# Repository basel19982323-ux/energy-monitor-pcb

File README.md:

# ESP32-C3 Solar Energy Monitor (PCB)

A 2-layer, 60 × 38 mm board that measures the **voltage, current and power** of a 50 W / 12 V solar panel and reports them over **Wi-Fi**.

> **Status:** designed and checked in KiCad 10 (ERC 0 errors, DRC 0 errors, 0 unconnected). **Not yet fabricated or tested on hardware.** Firmware (C, ESP-IDF) is written and tested in simulation: see [Firmware](#firmware).

| Top | Bottom |
|---|---|
|  |  |

---

## What it does

The panel's current flows through the board, from **J2 (Solar IN)** to **J3 (Load OUT)**, through a small 20 mΩ shunt resistor. The board works in five steps:

1. **Feed:** 5 V comes in through USB-C (J1). R1/R2 (5.1 kΩ on CC1/CC2) tell the USB source that this is a 5 V sink.
2. **Clean:** an AP2112K-3.3 LDO regulator (U2) makes a steady 3.3 V supply.
3. **Measure:** an INA226 (U1) measures the panel voltage and the current through the 20 mΩ shunt (R3).
4. **Think:** an ESP32-C3-WROOM-02 module (U3) reads the INA226 over I²C (address 0x40) and calculates power.
5. **Send:** the ESP32-C3 sends the readings over Wi-Fi. USB data (D+/D−) goes to the ESP32-C3's native USB for programming.

## Key numbers

| Item | Value |
|---|---|
| Target panel | 50 W, 12 V (Imp 2.84 A, Isc 3.13 A, Voc 20.8 V) |
| Shunt | 20 mΩ, 2512, 1 %, 2 W, Kelvin-connected |
| Max measurable current | 81.92 mV ÷ 0.02 Ω ≈ **4.1 A** (INA226 full-scale shunt voltage) |
| Shunt power at 4.1 A | 4.1² × 0.02 ≈ 0.34 W (well below the 2 W rating) |
| Logic supply | 5 V USB-C → 3.3 V (AP2112K, 600 mA max) |
| Board | 2 layers, 1.6 mm, 60 × 38 mm |

## Design decisions

- **Trace widths by net class** (IPC-2221): signals 0.25 mm, power (VBUS, +3V3) 0.5 mm, high current (PV_IN, LOAD_OUT) 2.1 mm for ~4 A.
- **Kelvin sensing:** the INA226 sense traces leave from the inner edges of the shunt pads, so the high current does not flow through the measurement traces.
- **Ground:** ground pours on both layers, joined by stitching vias, so every return current has a short path home.
- **Decoupling:** 100 nF + 10 µF placed at the ESP32-C3 3V3 pin (smallest capacitor closest), 100 nF at the INA226, 1 µF at the LDO input and output.
- **Antenna:** the ESP32-C3 antenna overhangs the board edge with no copper underneath, following Espressif's layout guidelines.
- **Boot and reset:** RESET (EN) with an RC start-up delay (10 kΩ + 1 µF), a BOOT button on IO9, and pull-ups on the strapping pins IO2/IO8/IO9.
- **Manufacturing:** checked against JLCPCB's capabilities (0.2 mm clearance, 0.3 mm vias, 0.15 mm silkscreen line width).

## Firmware

C firmware for the ESP32-C3 (ESP-IDF + FreeRTOS), tested in the Wokwi simulator with a simulated INA226. Not yet run on the real board. Full details, code structure and test results: **[firmware/README.md](firmware/README.md)**.

- Reads voltage, current and power from the INA226 over I²C every second (CAL = 2048 → 125 µA per bit)
- Latched alarm on overcurrent (> 3.5 A), overvoltage (> 22 V) or a missing sensor; reset with the BOOT button
- Re-writes the INA226 calibration automatically after the sensor stops answering and comes back
- Publishes the readings as JSON over Wi-Fi + MQTT
- 9 simulation tests (normal, faults, latch, reset, sensor removed, Wi-Fi): all pass

## Repository contents

```
hardware/     KiCad 10 project (schematic, PCB, project file)
production/   JLCPCB-ready files: Gerbers + drill (zip), BOM, CPL (positions)
firmware/     ESP32-C3 firmware (ESP-IDF, C) + Wokwi simulation files
docs/         Schematic PDF, 3D renders, layout preview, firmware screenshot
```

- **Schematic (PDF):** [docs/energy-monitor.pdf](docs/energy-monitor.pdf)
- **Gerbers + drill:** [production/energy-monitor_v0.2.zip](production/energy-monitor_v0.2.zip)
- **BOM** (with LCSC part numbers): [production/energy-monitor_v0.2_bom.csv](production/energy-monitor_v0.2_bom.csv)
- **CPL / pick-and-place:** [production/energy-monitor_v0.2_positions.csv](production/energy-monitor_v0.2_positions.csv)

## Bill of materials (summary)

| Ref | Part | LCSC |
|---|---|---|
| U1 | TI INA226AIDGSR (current/power monitor) | C49851 |
| U2 | Diodes AP2112K-3.3TRG1 (3.3 V LDO) | C51118 |
| U3 | Espressif ESP32-C3-WROOM-02-N4 | C2934560 |
| J1 | HRO TYPE-C-31-M-12 (USB-C) | C165948 |
| J2, J3 | Phoenix MKDS 1,5/2-5,08 terminal block | C480516 |
| R3 | 20 mΩ 2512 2 W shunt | C5375423 |
| SW1, SW2 | Omron B3F-1020 tactile switch | C722171 |
| R, C | 0805 passives (see BOM) | — |

## Notes

- The 3D model of the USB-C connector is not included (it is not from the official KiCad library), so J1 appears without a body in the 3D viewer. The PCB and fabrication files are not affected.
- Next steps: order the boards, run the firmware on real hardware and compare the readings against a reference meter, and add a status LED (rev 0.3).

## Tools

KiCad 10 · JLCPCB design rules · Fabrication Toolkit plugin · ESP-IDF (C, FreeRTOS) · Wokwi simulator

## License

Hardware design licensed under the **CERN Open Hardware Licence v2 – Permissive** ([CERN-OHL-P-2.0](LICENSE)). Firmware licensed under **MIT** ([firmware/LICENSE](firmware/LICENSE)).

© 2026 Basel Haijar

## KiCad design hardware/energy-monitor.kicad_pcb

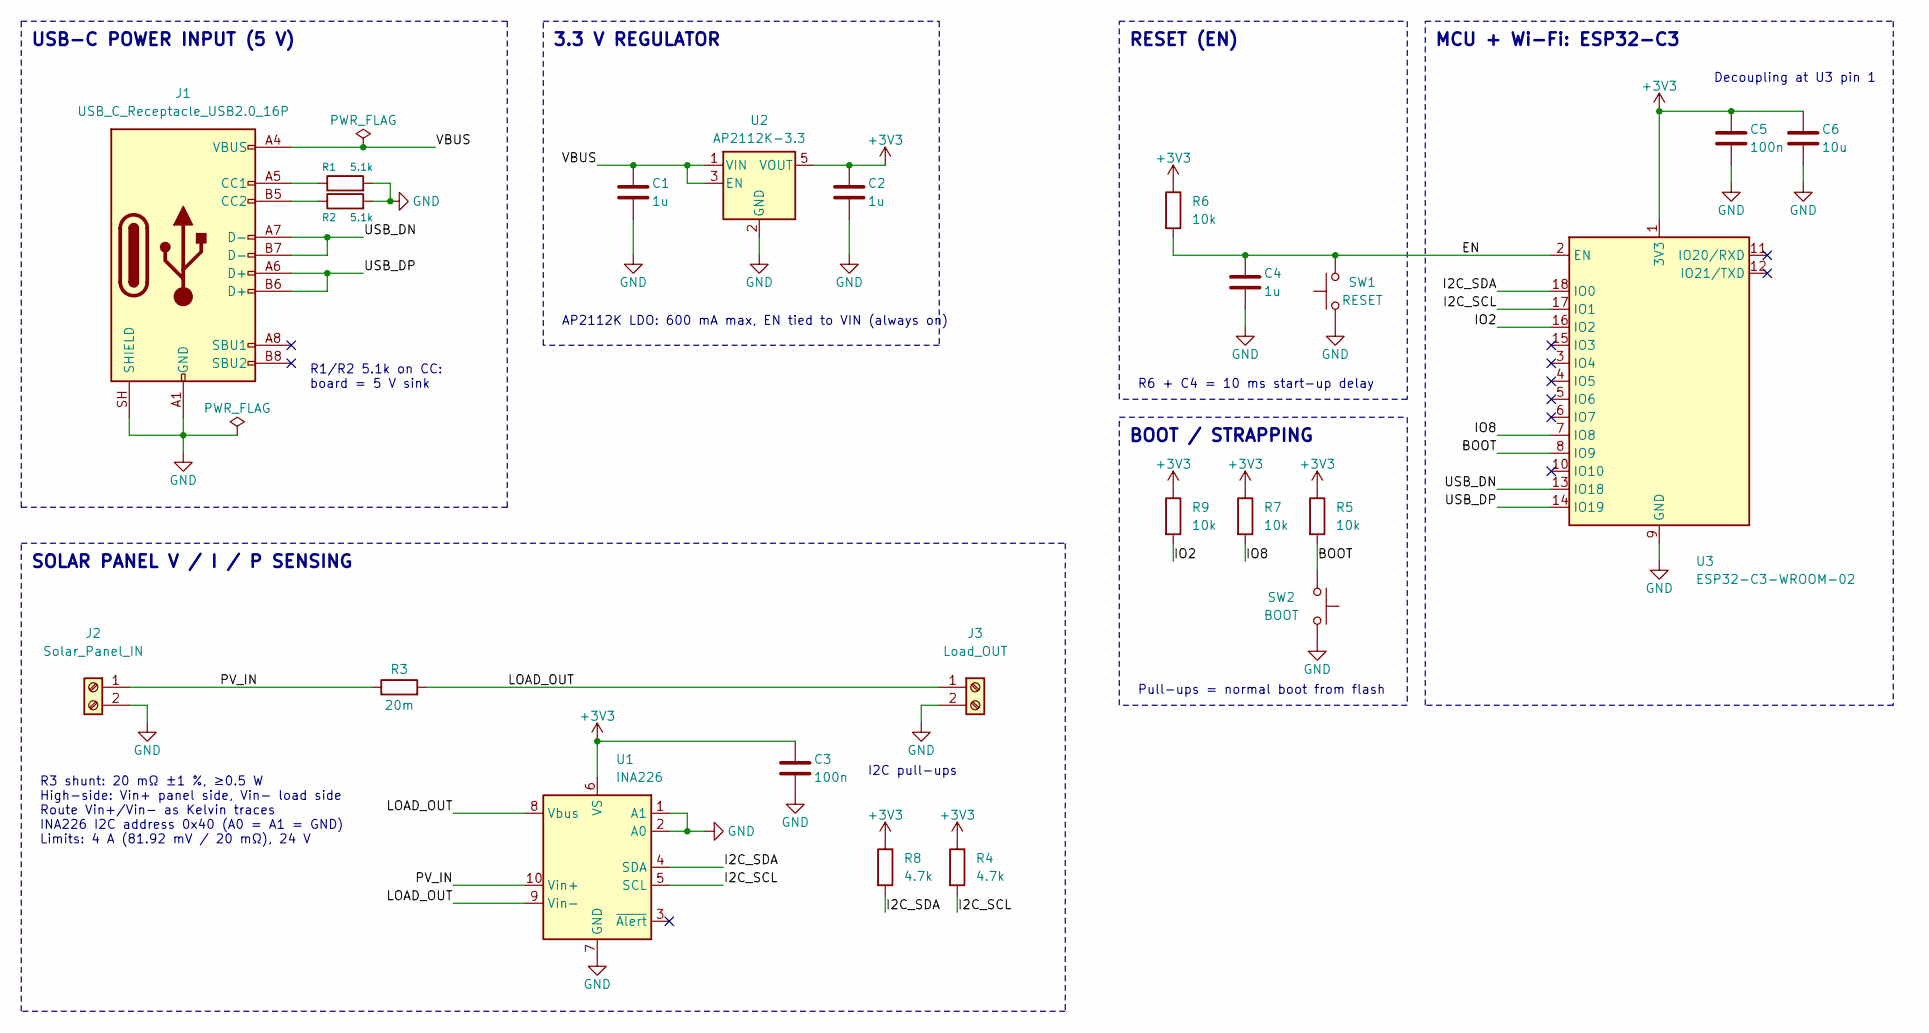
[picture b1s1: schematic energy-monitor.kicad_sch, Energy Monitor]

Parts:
C1, C2, C4: 1u; C_0805_2012Metric; LCSC C28323
C3, C5: 100n; C_0805_2012Metric; LCSC C49678
C6: 10u; C_0805_2012Metric; LCSC C15850
J1: USB_C_Receptacle_USB2.0_16P; USB_C_Receptacle_HRO_TYPE-C-31-M-12; LCSC C165948
J2: Solar_Panel_IN; TerminalBlock_Phoenix_MKDS-1,5-2-5.08_1x02_P5.08mm_Horizont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; LCSC C480516
J3: Load_OUT; TerminalBlock_Phoenix_MKDS-1,5-2-5.08_1x02_P5.08mm_Horizont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; LCSC C480516
R1, R2: 5.1k; R_0805_2012Metric; LCSC C27834
R3: 20m; R_2512_6332Metric; LCSC C5375423
R4, R8: 4.7k; R_0805_2012Metric; LCSC C17673
R5, R6, R7, R9: 10k; R_0805_2012Metric; LCSC C17414
SW1: RESET; SW_PUSH_6mm; LCSC C722171
SW2: BOOT; SW_PUSH_6mm; LCSC C722171
U1: INA226; TSSOP-10_3x3mm_P0.5mm; LCSC C49851
U2: AP2112K-3.3; SOT-23-5; LCSC C51118
U3: ESP32-C3-WROOM-02; LCSC C2934560

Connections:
+3V3: C2.1, C3.1, C5.1, C6.1, R4.1, R5.1, R6.1, R7.1, R8.1, R9.1, U1.6 (VS), U2.5 (VOUT), U3.1 (3V3)
/BOOT: R5.2, SW2.1, U3.8 (IO9)
/EN: C4.1, R6.2, SW1.2, U3.2 (EN)
/I2C_SCL: R4.2, U1.5 (SCL), U3.17 (IO1)
/I2C_SDA: R8.2, U1.4 (SDA), U3.18 (IO0)
/IO2: R9.2, U3.16 (IO2)
/IO8: R7.2, U3.7 (IO8)
/LOAD_OUT: J3.1, R3.2, U1.8 (Vbus), U1.9 (Vin-)
/PV_IN: J2.1, R3.1, U1.10 (Vin+)
/USB_DN: J1.A7 (D-), J1.B7 (D-), U3.13 (IO18)
/USB_DP: J1.A6 (D+), J1.B6 (D+), U3.14 (IO19)
/VBUS: C1.1, J1.A4 (VBUS), J1.A9 (VBUS), J1.B4 (VBUS), J1.B9 (VBUS), U2.1 (VIN), U2.3 (EN)
GND: C1.2, C2.2, C3.2, C4.2, C5.2, C6.2, J1.A1 (GND), J1.A12 (GND), J1.B1 (GND), J1.B12 (GND), J1.SH (SHIELD), J2.2, J3.2, R1.2, R2.2, SW1.1, SW2.2, U1.1 (A1), U1.2 (A0), U1.7 (GND), U2.2 (GND), U3.9 (GND), U3.19 (GND)
unnamed: J1.A5 (CC1), R1.1
unnamed: J1.B5 (CC2), R2.1

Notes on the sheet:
I2C pull-ups
RESET (EN)
BOOT / STRAPPING
Decoupling at U3 pin 1
R1/R2 5.1k on CC: board = 5 V sink
MCU + Wi-Fi: ESP32-C3
SOLAR PANEL V / I / P SENSING
R3 shunt: 20 mΩ ±1 %, ≥0.5 W High-side: Vin+ panel side, Vin− load side Route Vin+/Vin− as Kelvin traces INA226 I2C address 0x40 (A0 = A1 = GND) Limits: 4 A (81.92 mV / 20 mΩ), 24 V
USB-C POWER INPUT (5 V)
AP2112K LDO: 600 mA max, EN tied to VIN (always on)
Pull-ups = normal boot from flash
3.3 V REGULATOR
R6 + C4 = 10 ms start-up delay

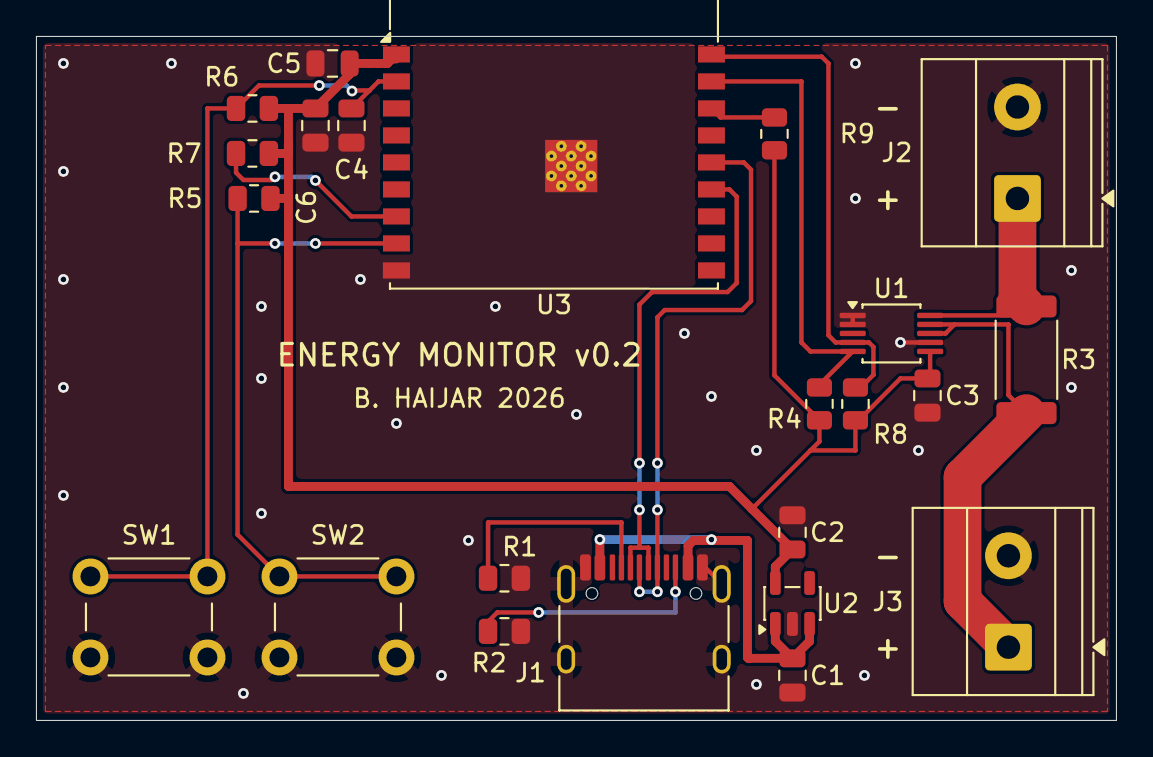
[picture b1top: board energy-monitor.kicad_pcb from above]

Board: 2 copper layers, 60.0 x 38.0 mm, 23 parts (0 on the bottom side), 15 nets.

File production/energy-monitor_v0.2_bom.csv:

Designator,Footprint,Quantity,Value,LCSC Part #
"C1, C2, C4",0805,3,1u,C28323
"C3, C5",0805,2,100n,C49678
C6,0805,1,10u,C15850
J1,USB_C_Receptacle_HRO_TYPE-C-31-M-12,1,USB_C_Receptacle_USB2.0_16P,C165948
J2,"TerminalBlock_Phoenix_MKDS-1,5-2-5.08_1x02_P5.08mm_Horizontal",1,Solar_Panel_IN,C480516
J3,"TerminalBlock_Phoenix_MKDS-1,5-2-5.08_1x02_P5.08mm_Horizontal",1,Load_OUT,C480516
"R1, R2",0805,2,5.1k,C27834
R3,2512,1,20m,C5375423
"R4, R8",0805,2,4.7k,C17673
"R5, R6, R7, R9",0805,4,10k,C17414
SW1,SW_PUSH_6mm,1,RESET,C722171
SW2,SW_PUSH_6mm,1,BOOT,C722171
U1,TSSOP-10_3x3mm_P0.5mm,1,INA226,C49851
U2,SOT-23-5,1,AP2112K-3.3,C51118
U3,ESP32-C3-WROOM-02,1,ESP32-C3-WROOM-02,C2934560
